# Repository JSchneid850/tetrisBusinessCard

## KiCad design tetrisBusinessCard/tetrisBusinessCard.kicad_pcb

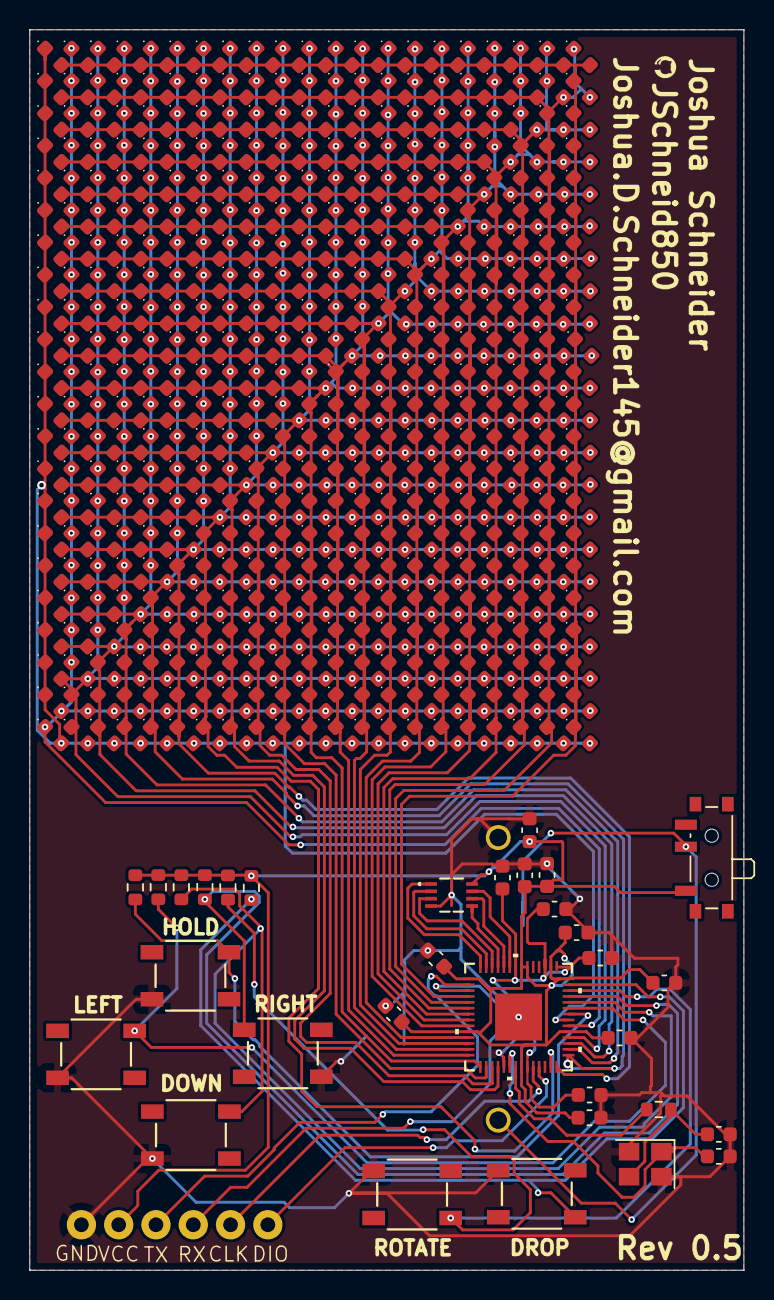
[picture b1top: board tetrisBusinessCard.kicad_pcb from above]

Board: 2 copper layers, 48.7 x 84.5 mm, 497 parts (1 on the bottom side), 45 nets.

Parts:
B1: BS-02-A1BK007; BAT_BS-02_MYG-NoDrill
C1, C2, C3, C4, C5, C7, C9, C10, C11, C12, C13: 100n; C_0603_1608Metric
C6, C8: 1u; C_0603_1608Metric
C16, C17: 15p; C_0603_1608Metric
D1, D2, D3, D4, D5, D6, D7, D8, D9, D10, D11, D12, D13, D14, D15, D16, D17, D18, D19, D20, D21, D22, D23, D24, D25, D26, D27, D28, D29, D30, D31, D32, D33, D34, D35, D36, D37, D38, D39, D40, D41, D42, D43, D44, D45, D46, D47, D48, D49, D50, D51, D52, D53, D54, D55, D56, D57, D58, D59, D60, D61, D62, D63, D64, D65, D66, D67, D68, D69, D70, D71, D72, D73, D74, D75, D76, D77, D78, D79, D80, D81, D82, D83, D84, D85, D86, D87, D88, D89, D90, D91, D92, D93, D94, D95, D96, D97, D98, D99, D100, D101, D102, D103, D104, D105, D106, D107, D108, D109, D110, D111, D112, D113, D114, D115, D116, D117, D118, D119, D120, D121, D122, D123, D124, D125, D126, D127, D128, D129, D130, D131, D132, D133, D134, D135, D136, D137, D138, D139, D140, D141, D142, D143, D144, D145, D146, D147, D148, D149, D150, D151, D152, D153, D154, D155, D156, D157, D158, D159, D160, D161, D162, D163, D164, D165, D166, D167, D168, D169, D170, D171, D172, D173, D174, D175, D176, D177, D178, D179, D180, D181, D182, D183, D184, D185, D186, D187, D188, D189, D190, D191, D192, D193, D194, D195, D196, D197, D198, D199, D200, D201, D202, D203, D204, D205, D206, D207, D208, D209, D210, D211, D212, D213, D214, D215, D216, D217, D218, D219, D220, D221, D222, D223, D224, D225, D226, D227, D228, D229, D230, D231, D232, D233, D234, D235, D236, D237, D238, D239, D240, D241, D242, D243, D244, D245, D246, D247, D248, D249, D250, D251, D252, D253, D254, D255, D256, D257, D258, D259, D260, D261, D262, D263, D264, D265, D266, D267, D268, D269, D270, D271, D272, D273, D274, D275, D276, D277, D278, D279, D280, D281, D282, D283, D284, D285, D286, D287, D288, D289, D290, D291, D292, D293, D294, D295, D296, D297, D298, D299, D300, D301, D302, D303, D304, D305, D306, D307, D308, D309, D310, D311, D312, D313, D314, D315, D316, D317, D318, D319, D320, D321, D322, D323, D324, D325, D326, D327, D328, D329, D330, D331, D332, D333, D334, D335, D336, D337, D338, D339, D340, D341, D342, D343, D344, D345, D346, D347, D348, D349, D350, D351, D352, D353, D354, D355, D356, D357, D358, D359, D360, D361, D362, D363, D364, D365, D366, D367, D368, D369, D370, D371, D372, D373, D374, D375, D376, D377, D378, D379, D380, D381, D382, D383, D384, D385, D386, D387, D388, D389, D390, D391, D392, D393, D394, D395, D396, D397, D398, D399, D400, D401, D402, D403, D404, D405, D406, D407, D408, D409, D410, D411, D412, D413, D414, D415, D416, D417, D418, D419, D420, D421, D422, D423, D424, D425, D426, D427, D428, D429, D430, D431, D432, D433, D434, D435, D436, D437, D438, D439, D440, D441, D442, D443, D444, D445, D446, D447, D448, D449, D450, D451, D452, D453, D454, D455, D456, D457, D458, D459, D460, D461, D462: LED; LED_0603_1608MetricAdjusted
Github: LOGO; 2mgh
PogoConnector1: PogoConnector
R5: 1kΩ; R_0603_1608Metric
R6, R7, R8, R9, R10, R11: 10kΩ; R_0603_1608Metric
SW1, SW2, SW3, SW4, SW5, SW6: SW_Push; SW_PTS647SM38SMTR2LFS_CNK
SW7: SW_DPST_x2; SW_SPDT_PCM12
U1: SC091413; QFN56_7X7_RPI
U2: W25Q16JVUXIQ; W25Q16JVUXIQ_WIN
Y1: ABMB-272-T3; Crystal_SMD_3225-4Pin_3.2x2.5mm

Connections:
+1V1: C1.2, C6.2, C7.2, C12.1, U1.23 (DVDD), U1.43 (ADC_AVDD), U1.45 (VREG_VOUT), U1.50 (DVDD)
BATT +: C2.2, C3.2, C4.2, C5.2, C8.2, C9.2, C10.1, C11.1, C13.1, PogoConnector1.2, R6.1, R7.1, R8.1, R9.1, R10.1, R11.1, SW7.1 (A), U1.1 (IOVDD), U1.10 (IOVDD), U1.22 (IOVDD), U1.33 (IOVDD), U1.42 (IOVDD), U1.44 (VREG_VIN), U1.48 (USB_VDD), U1.49 (IOVDD), U2.8 (VCC)
BTN_1: R10.2, SW1.3, U1.36 (GPIO24)
BTN_2: R9.2, SW2.3, U1.37 (GPIO25)
BTN_3: R8.2, SW3.3, U1.38 (GPIO26/ADC0)
BTN_4: R7.2, SW4.1, U1.39 (GPIO27/ADC1)
BTN_5: R6.2, SW5.1, U1.40 (GPIO28/ADC2)
BTN_6: R11.2, SW6.1, U1.41 (GPIO29/ADC3)
CHRLY_1: D1.2 (A), D2.2 (A), D3.2 (A), D4.2 (A), D5.2 (A), D6.2 (A), D7.2 (A), D8.2 (A), D9.2 (A), D10.2 (A), D11.2 (A), D12.2 (A), D13.2 (A), D14.2 (A), D15.2 (A), D16.2 (A), D17.2 (A), D18.2 (A), D19.2 (A), D20.2 (A), D21.2 (A), D22.1 (K), D43.1 (K), D64.1 (K), D85.1 (K), D106.1 (K), D127.1 (K), D148.1 (K), D169.1 (K), D190.1 (K), D211.1 (K), D232.1 (K), D253.1 (K), D274.1 (K), D295.1 (K), D316.1 (K), D337.1 (K), D358.1 (K), D379.1 (K), D400.1 (K), D421.1 (K), D442.1 (K), U1.4 (GPIO2)
CHRLY_2: D1.1 (K), D22.2 (A), D23.2 (A), D24.2 (A), D25.2 (A), D26.2 (A), D27.2 (A), D28.2 (A), D29.2 (A), D30.2 (A), D31.2 (A), D32.2 (A), D33.2 (A), D34.2 (A), D35.2 (A), D36.2 (A), D37.2 (A), D38.2 (A), D39.2 (A), D40.2 (A), D41.2 (A), D42.2 (A), D44.1 (K), D65.1 (K), D86.1 (K), D107.1 (K), D128.1 (K), D149.1 (K), D170.1 (K), D191.1 (K), D212.1 (K), D233.1 (K), D254.1 (K), D275.1 (K), D296.1 (K), D317.1 (K), D338.1 (K), D359.1 (K), D380.1 (K), D401.1 (K), D422.1 (K), D443.1 (K), U1.5 (GPIO3)
CHRLY_3: D2.1 (K), D23.1 (K), D43.2 (A), D44.2 (A), D45.2 (A), D46.2 (A), D47.2 (A), D48.2 (A), D49.2 (A), D50.2 (A), D51.2 (A), D52.2 (A), D53.2 (A), D54.2 (A), D55.2 (A), D56.2 (A), D57.2 (A), D58.2 (A), D59.2 (A), D60.2 (A), D61.2 (A), D62.2 (A), D63.2 (A), D66.1 (K), D87.1 (K), D108.1 (K), D129.1 (K), D150.1 (K), D171.1 (K), D192.1 (K), D213.1 (K), D234.1 (K), D255.1 (K), D276.1 (K), D297.1 (K), D318.1 (K), D339.1 (K), D360.1 (K), D381.1 (K), D402.1 (K), D423.1 (K), D444.1 (K), U1.6 (GPIO4)
CHRLY_4: D3.1 (K), D24.1 (K), D45.1 (K), D64.2 (A), D65.2 (A), D66.2 (A), D67.2 (A), D68.2 (A), D69.2 (A), D70.2 (A), D71.2 (A), D72.2 (A), D73.2 (A), D74.2 (A), D75.2 (A), D76.2 (A), D77.2 (A), D78.2 (A), D79.2 (A), D80.2 (A), D81.2 (A), D82.2 (A), D83.2 (A), D84.2 (A), D88.1 (K), D109.1 (K), D130.1 (K), D151.1 (K), D172.1 (K), D193.1 (K), D214.1 (K), D235.1 (K), D256.1 (K), D277.1 (K), D298.1 (K), D319.1 (K), D340.1 (K), D361.1 (K), D382.1 (K), D403.1 (K), D424.1 (K), D445.1 (K), U1.7 (GPIO5)
CHRLY_5: D4.1 (K), D25.1 (K), D46.1 (K), D67.1 (K), D85.2 (A), D86.2 (A), D87.2 (A), D88.2 (A), D89.2 (A), D90.2 (A), D91.2 (A), D92.2 (A), D93.2 (A), D94.2 (A), D95.2 (A), D96.2 (A), D97.2 (A), D98.2 (A), D99.2 (A), D100.2 (A), D101.2 (A), D102.2 (A), D103.2 (A), D104.2 (A), D105.2 (A), D110.1 (K), D131.1 (K), D152.1 (K), D173.1 (K), D194.1 (K), D215.1 (K), D236.1 (K), D257.1 (K), D278.1 (K), D299.1 (K), D320.1 (K), D341.1 (K), D362.1 (K), D383.1 (K), D404.1 (K), D425.1 (K), D446.1 (K), U1.8 (GPIO6)
CHRLY_6: D5.1 (K), D26.1 (K), D47.1 (K), D68.1 (K), D89.1 (K), D106.2 (A), D107.2 (A), D108.2 (A), D109.2 (A), D110.2 (A), D111.2 (A), D112.2 (A), D113.2 (A), D114.2 (A), D115.2 (A), D116.2 (A), D117.2 (A), D118.2 (A), D119.2 (A), D120.2 (A), D121.2 (A), D122.2 (A), D123.2 (A), D124.2 (A), D125.2 (A), D126.2 (A), D132.1 (K), D153.1 (K), D174.1 (K), D195.1 (K), D216.1 (K), D237.1 (K), D258.1 (K), D279.1 (K), D300.1 (K), D321.1 (K), D342.1 (K), D363.1 (K), D384.1 (K), D405.1 (K), D426.1 (K), D447.1 (K), U1.9 (GPIO7)
CHRLY_7: D6.1 (K), D27.1 (K), D48.1 (K), D69.1 (K), D90.1 (K), D111.1 (K), D127.2 (A), D128.2 (A), D129.2 (A), D130.2 (A), D131.2 (A), D132.2 (A), D133.2 (A), D134.2 (A), D135.2 (A), D136.2 (A), D137.2 (A), D138.2 (A), D139.2 (A), D140.2 (A), D141.2 (A), D142.2 (A), D143.2 (A), D144.2 (A), D145.2 (A), D146.2 (A), D147.2 (A), D154.1 (K), D175.1 (K), D196.1 (K), D217.1 (K), D238.1 (K), D259.1 (K), D280.1 (K), D301.1 (K), D322.1 (K), D343.1 (K), D364.1 (K), D385.1 (K), D406.1 (K), D427.1 (K), D448.1 (K), U1.11 (GPIO8)
CHRLY_8: D7.1 (K), D28.1 (K), D49.1 (K), D70.1 (K), D91.1 (K), D112.1 (K), D133.1 (K), D148.2 (A), D149.2 (A), D150.2 (A), D151.2 (A), D152.2 (A), D153.2 (A), D154.2 (A), D155.2 (A), D156.2 (A), D157.2 (A), D158.2 (A), D159.2 (A), D160.2 (A), D161.2 (A), D162.2 (A), D163.2 (A), D164.2 (A), D165.2 (A), D166.2 (A), D167.2 (A), D168.2 (A), D176.1 (K), D197.1 (K), D218.1 (K), D239.1 (K), D260.1 (K), D281.1 (K), D302.1 (K), D323.1 (K), D344.1 (K), D365.1 (K), D386.1 (K), D407.1 (K), D428.1 (K), D449.1 (K), U1.12 (GPIO9)
CHRLY_9: D8.1 (K), D29.1 (K), D50.1 (K), D71.1 (K), D92.1 (K), D113.1 (K), D134.1 (K), D155.1 (K), D169.2 (A), D170.2 (A), D171.2 (A), D172.2 (A), D173.2 (A), D174.2 (A), D175.2 (A), D176.2 (A), D177.2 (A), D178.2 (A), D179.2 (A), D180.2 (A), D181.2 (A), D182.2 (A), D183.2 (A), D184.2 (A), D185.2 (A), D186.2 (A), D187.2 (A), D188.2 (A), D189.2 (A), D198.1 (K), D219.1 (K), D240.1 (K), D261.1 (K), D282.1 (K), D303.1 (K), D324.1 (K), D345.1 (K), D366.1 (K), D387.1 (K), D408.1 (K), D429.1 (K), D450.1 (K), U1.13 (GPIO10)
CHRLY_10: D9.1 (K), D30.1 (K), D51.1 (K), D72.1 (K), D93.1 (K), D114.1 (K), D135.1 (K), D156.1 (K), D177.1 (K), D190.2 (A), D191.2 (A), D192.2 (A), D193.2 (A), D194.2 (A), D195.2 (A), D196.2 (A), D197.2 (A), D198.2 (A), D199.2 (A), D200.2 (A), D201.2 (A), D202.2 (A), D203.2 (A), D204.2 (A), D205.2 (A), D206.2 (A), D207.2 (A), D208.2 (A), D209.2 (A), D210.2 (A), D220.1 (K), D241.1 (K), D262.1 (K), D283.1 (K), D304.1 (K), D325.1 (K), D346.1 (K), D367.1 (K), D388.1 (K), D409.1 (K), D430.1 (K), D451.1 (K), U1.14 (GPIO11)
CHRLY_11: D10.1 (K), D31.1 (K), D52.1 (K), D73.1 (K), D94.1 (K), D115.1 (K), D136.1 (K), D157.1 (K), D178.1 (K), D199.1 (K), D211.2 (A), D212.2 (A), D213.2 (A), D214.2 (A), D215.2 (A), D216.2 (A), D217.2 (A), D218.2 (A), D219.2 (A), D220.2 (A), D221.2 (A), D222.2 (A), D223.2 (A), D224.2 (A), D225.2 (A), D226.2 (A), D227.2 (A), D228.2 (A), D229.2 (A), D230.2 (A), D231.2 (A), D242.1 (K), D263.1 (K), D284.1 (K), D305.1 (K), D326.1 (K), D347.1 (K), D368.1 (K), D389.1 (K), D410.1 (K), D431.1 (K), D452.1 (K), U1.15 (GPIO12)
CHRLY_12: D11.1 (K), D32.1 (K), D53.1 (K), D74.1 (K), D95.1 (K), D116.1 (K), D137.1 (K), D158.1 (K), D179.1 (K), D200.1 (K), D221.1 (K), D232.2 (A), D233.2 (A), D234.2 (A), D235.2 (A), D236.2 (A), D237.2 (A), D238.2 (A), D239.2 (A), D240.2 (A), D241.2 (A), D242.2 (A), D243.2 (A), D244.2 (A), D245.2 (A), D246.2 (A), D247.2 (A), D248.2 (A), D249.2 (A), D250.2 (A), D251.2 (A), D252.2 (A), D264.1 (K), D285.1 (K), D306.1 (K), D327.1 (K), D348.1 (K), D369.1 (K), D390.1 (K), D411.1 (K), D432.1 (K), D453.1 (K), U1.16 (GPIO13)
CHRLY_13: D12.1 (K), D33.1 (K), D54.1 (K), D75.1 (K), D96.1 (K), D117.1 (K), D138.1 (K), D159.1 (K), D180.1 (K), D201.1 (K), D222.1 (K), D243.1 (K), D253.2 (A), D254.2 (A), D255.2 (A), D256.2 (A), D257.2 (A), D258.2 (A), D259.2 (A), D260.2 (A), D261.2 (A), D262.2 (A), D263.2 (A), D264.2 (A), D265.2 (A), D266.2 (A), D267.2 (A), D268.2 (A), D269.2 (A), D270.2 (A), D271.2 (A), D272.2 (A), D273.2 (A), D286.1 (K), D307.1 (K), D328.1 (K), D349.1 (K), D370.1 (K), D391.1 (K), D412.1 (K), D433.1 (K), D454.1 (K), U1.17 (GPIO14)
CHRLY_14: D13.1 (K), D34.1 (K), D55.1 (K), D76.1 (K), D97.1 (K), D118.1 (K), D139.1 (K), D160.1 (K), D181.1 (K), D202.1 (K), D223.1 (K), D244.1 (K), D265.1 (K), D274.2 (A), D275.2 (A), D276.2 (A), D277.2 (A), D278.2 (A), D279.2 (A), D280.2 (A), D281.2 (A), D282.2 (A), D283.2 (A), D284.2 (A), D285.2 (A), D286.2 (A), D287.2 (A), D288.2 (A), D289.2 (A), D290.2 (A), D291.2 (A), D292.2 (A), D293.2 (A), D294.2 (A), D308.1 (K), D329.1 (K), D350.1 (K), D371.1 (K), D392.1 (K), D413.1 (K), D434.1 (K), D455.1 (K), U1.18 (GPIO15)
CHRLY_15: D14.1 (K), D35.1 (K), D56.1 (K), D77.1 (K), D98.1 (K), D119.1 (K), D140.1 (K), D161.1 (K), D182.1 (K), D203.1 (K), D224.1 (K), D245.1 (K), D266.1 (K), D287.1 (K), D295.2 (A), D296.2 (A), D297.2 (A), D298.2 (A), D299.2 (A), D300.2 (A), D301.2 (A), D302.2 (A), D303.2 (A), D304.2 (A), D305.2 (A), D306.2 (A), D307.2 (A), D308.2 (A), D309.2 (A), D310.2 (A), D311.2 (A), D312.2 (A), D313.2 (A), D314.2 (A), D315.2 (A), D330.1 (K), D351.1 (K), D372.1 (K), D393.1 (K), D414.1 (K), D435.1 (K), D456.1 (K), U1.27 (GPIO16)
CHRLY_16: D15.1 (K), D36.1 (K), D57.1 (K), D78.1 (K), D99.1 (K), D120.1 (K), D141.1 (K), D162.1 (K), D183.1 (K), D204.1 (K), D225.1 (K), D246.1 (K), D267.1 (K), D288.1 (K), D309.1 (K), D316.2 (A), D317.2 (A), D318.2 (A), D319.2 (A), D320.2 (A), D321.2 (A), D322.2 (A), D323.2 (A), D324.2 (A), D325.2 (A), D326.2 (A), D327.2 (A), D328.2 (A), D329.2 (A), D330.2 (A), D331.2 (A), D332.2 (A), D333.2 (A), D334.2 (A), D335.2 (A), D336.2 (A), D352.1 (K), D373.1 (K), D394.1 (K), D415.1 (K), D436.1 (K), D457.1 (K), U1.28 (GPIO17)
CHRLY_17: D16.1 (K), D37.1 (K), D58.1 (K), D79.1 (K), D100.1 (K), D121.1 (K), D142.1 (K), D163.1 (K), D184.1 (K), D205.1 (K), D226.1 (K), D247.1 (K), D268.1 (K), D289.1 (K), D310.1 (K), D331.1 (K), D337.2 (A), D338.2 (A), D339.2 (A), D340.2 (A), D341.2 (A), D342.2 (A), D343.2 (A), D344.2 (A), D345.2 (A), D346.2 (A), D347.2 (A), D348.2 (A), D349.2 (A), D350.2 (A), D351.2 (A), D352.2 (A), D353.2 (A), D354.2 (A), D355.2 (A), D356.2 (A), D357.2 (A), D374.1 (K), D395.1 (K), D416.1 (K), D437.1 (K), D458.1 (K), U1.29 (GPIO18)
CHRLY_18: D17.1 (K), D38.1 (K), D59.1 (K), D80.1 (K), D101.1 (K), D122.1 (K), D143.1 (K), D164.1 (K), D185.1 (K), D206.1 (K), D227.1 (K), D248.1 (K), D269.1 (K), D290.1 (K), D311.1 (K), D332.1 (K), D353.1 (K), D358.2 (A), D359.2 (A), D360.2 (A), D361.2 (A), D362.2 (A), D363.2 (A), D364.2 (A), D365.2 (A), D366.2 (A), D367.2 (A), D368.2 (A), D369.2 (A), D370.2 (A), D371.2 (A), D372.2 (A), D373.2 (A), D374.2 (A), D375.2 (A), D376.2 (A), D377.2 (A), D378.2 (A), D396.1 (K), D417.1 (K), D438.1 (K), D459.1 (K), U1.30 (GPIO19)
CHRLY_19: D18.1 (K), D39.1 (K), D60.1 (K), D81.1 (K), D102.1 (K), D123.1 (K), D144.1 (K), D165.1 (K), D186.1 (K), D207.1 (K), D228.1 (K), D249.1 (K), D270.1 (K), D291.1 (K), D312.1 (K), D333.1 (K), D354.1 (K), D375.1 (K), D379.2 (A), D380.2 (A), D381.2 (A), D382.2 (A), D383.2 (A), D384.2 (A), D385.2 (A), D386.2 (A), D387.2 (A), D388.2 (A), D389.2 (A), D390.2 (A), D391.2 (A), D392.2 (A), D393.2 (A), D394.2 (A), D395.2 (A), D396.2 (A), D397.2 (A), D398.2 (A), D399.2 (A), D418.1 (K), D439.1 (K), D460.1 (K), U1.31 (GPIO20)
CHRLY_20: D19.1 (K), D40.1 (K), D61.1 (K), D82.1 (K), D103.1 (K), D124.1 (K), D145.1 (K), D166.1 (K), D187.1 (K), D208.1 (K), D229.1 (K), D250.1 (K), D271.1 (K), D292.1 (K), D313.1 (K), D334.1 (K), D355.1 (K), D376.1 (K), D397.1 (K), D400.2 (A), D401.2 (A), D402.2 (A), D403.2 (A), D404.2 (A), D405.2 (A), D406.2 (A), D407.2 (A), D408.2 (A), D409.2 (A), D410.2 (A), D411.2 (A), D412.2 (A), D413.2 (A), D414.2 (A), D415.2 (A), D416.2 (A), D417.2 (A), D418.2 (A), D419.2 (A), D420.2 (A), D440.1 (K), D461.1 (K), U1.32 (GPIO21)
CHRLY_21: D20.1 (K), D41.1 (K), D62.1 (K), D83.1 (K), D104.1 (K), D125.1 (K), D146.1 (K), D167.1 (K), D188.1 (K), D209.1 (K), D230.1 (K), D251.1 (K), D272.1 (K), D293.1 (K), D314.1 (K), D335.1 (K), D356.1 (K), D377.1 (K), D398.1 (K), D419.1 (K), D421.2 (A), D422.2 (A), D423.2 (A), D424.2 (A), D425.2 (A), D426.2 (A), D427.2 (A), D428.2 (A), D429.2 (A), D430.2 (A), D431.2 (A), D432.2 (A), D433.2 (A), D434.2 (A), D435.2 (A), D436.2 (A), D437.2 (A), D438.2 (A), D439.2 (A), D440.2 (A), D441.2 (A), D462.1 (K), U1.34 (GPIO22)
CHRLY_22: D21.1 (K), D42.1 (K), D63.1 (K), D84.1 (K), D105.1 (K), D126.1 (K), D147.1 (K), D168.1 (K), D189.1 (K), D210.1 (K), D231.1 (K), D252.1 (K), D273.1 (K), D294.1 (K), D315.1 (K), D336.1 (K), D357.1 (K), D378.1 (K), D399.1 (K), D420.1 (K), D441.1 (K), D442.2 (A), D443.2 (A), D444.2 (A), D445.2 (A), D446.2 (A), D447.2 (A), D448.2 (A), D449.2 (A), D450.2 (A), D451.2 (A), D452.2 (A), D453.2 (A), D454.2 (A), D455.2 (A), D456.2 (A), D457.2 (A), D458.2 (A), D459.2 (A), D460.2 (A), D461.2 (A), D462.2 (A), U1.35 (GPIO23)
GND: B1.2, C1.1, C2.1, C3.1, C4.1, C5.1, C6.1, C7.1, C8.1, C9.1, C10.2, C11.2, C12.2, C13.2, C16.2, C17.2, PogoConnector1.1, SW1.2, SW2.2, SW3.2, SW4.4, SW5.4, SW6.4, U1.19 (TESTEN), U1.57 (GND), U2.4 (GND), U2.9 (EPAD), Y1.2, Y1.4
unnamed: C17.1, R5.2, Y1.3
unnamed: B1.1, SW7.2 (B)
unnamed: U1.52 (SQPI_SCLK), U2.6 (CLK)
unnamed: U1.53 (SQPI_SD0), U2.5 (DI(IO0))
unnamed: U1.55 (SQPI_SD1), U2.2 (DO(IO1))
unnamed: U1.54 (SQPI_SD2), U2.3 (/WP(IO2))
unnamed: U1.51 (SQPI_SD3), U2.7 (/HOLD_or_/RESET(IO3))
unnamed: U1.56 (SQPI_SS_N), U2.1 (/CS)
RX: PogoConnector1.4, U1.3 (GPIO1)
SWCLK: PogoConnector1.5, U1.24 (SWCLK)
SWDIO: PogoConnector1.6, U1.25 (SWDIO)
TX: PogoConnector1.3, U1.2 (GPIO0)
XIn: C16.1, U1.20 (XIN), Y1.1
Xout: R5.1, U1.21 (XOUT)

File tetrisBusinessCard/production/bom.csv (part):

Designator,Footprint,Quantity,Value,LCSC Part #
"B1_8, B1_7, B1_6, B1_5, B1_4, B1_3, B1_2, B1",BAT_BS-02_MYG-NoDrill,8,BS-02-A1BK007,
"C1_8, C1_7, C1_6, C1_5, C1_4, C1_3, C1_2, C1, C10_8, C10_7, C10_6, C10_5, C10_4, C10_3, C10_2, C10, C11_8, C11_7, C11_6, C11_5, C11_4, C11_3, C11_2, C11, C12_8, C12_7, C12_6, C12_5, C12_4, C12_3, C12_2, C12, C13_8, C13_7, C13_6, C13_5, C13_4, C13_3, C13_2, C13, C2_8, C2_7, C2_6, C2_5, C2_4, C2_3, C2_2, C2, C3_8, C3_7, C3_6, C3_5, C3_4, C3_3, C3_2, C3, C4_8, C4_7, C4_6, C4_5, C4_4, C4_3, C4_2, C4, C5_8, C5_7, C5_6, C5_5, C5_4, C5_3, C5_2, C5, C7_8, C7_7, C7_6, C7_5, C7_4, C7_3, C7_2, C7, C9_8, C9_7, C9_6, C9_5, C9_4, C9_3, C9_2, C9",0603,88,100n,
"C16_8, C16_7, C16_6, C16_5, C16_4, C16_3, C16_2, C16, C17_8, C17_7, C17_6, C17_5, C17_4, C17_3, C17_2, C17",0603,16,15p,
"C6_8, C6_7, C6_6, C6_5, C6_4, C6_3, C6_2, C6, C8_8, C8_7, C8_6, C8_5, C8_4, C8_3, C8_2, C8",0603,16,1u,
"D1_8, D1_7, D1_6, D1_5, D1_4, D1_3, D1_2, D1, D10_8, D10_7, D10_6, D10_5, D10_4, D10_3, D10_2, D10, D100_8, D100_7, D100_6, D100_5, D100_4, D100_3, D100_2, D100, D101_8, D101_7, D101_6, D101_5, D101_4, D101_3, D101_2, D101, D102_8, D102_7, D102_6, D102_5, D102_4, D102_3, D102_2, D102, D103_8, D103_7, D103_6, D103_5, D103_4, D103_3, D103_2, D103, D104_8, D104_7, D104_6, D104_5, D104_4, D104_3, D104_2, D104, D105_8, D105_7, D105_6, D105_5, D105_4, D105_3, D105_2, D105, D106_8, D106_7, D106_6, D106_5, D106_4, D106_3, D106_2, D106, D107_8, D107_7, D107_6, D107_5, D107_4, D107_3, D107_2, D107, D108_8, D108_7, D108_6, D108_5, D108_4, D108_3, D108_2, D108, D109_8, D109_7, D109_6, D109_5, D109_4, D109_3, D109_2, D109, D11_8, D11_7, D11_6, D11_5, D11_4, D11_3, D11_2, D11, D110_8, D110_7, D110_6, D110_5, D110_4, D110_3, D110_2, D110, D111_8, D111_7, D111_6, D111_5, D111_4, D111_3, D111_2, D111, D112_8, D112_7, D112_6, D112_5, D112_4, D112_3, D112_2, D112, D113_8, D113_7, D113_6, D113_5, D113_4, D113_3, D113_2, D113, D114_8, D114_7, D114_6, D114_5, D114_4, D114_3, D114_2, D114, D115_8, D115_7, D115_6, D115_5, D115_4, D115_3, D115_2, D115, D116_8, D116_7, D116_6, D116_5, D116_4, D116_3, D116_2, D116, D117_8, D117_7, D117_6, D117_5, D117_4, D117_3, D117_2, D117, D118_8, D118_7, D118_6, D118_5, D118_4, D118_3, D118_2, D118, D119_8, D119_7, D119_6, D119_5, D119_4, D119_3, D119_2, D119, D12_8, D12_7, D12_6, D12_5, D12_4, D12_3, D12_2, D12, D120_8, D120_7, D120_6, D120_5, D120_4, D120_3, D120_2, D120",0603,200,LED,
"D121_8, D121_7, D121_6, D121_5, D121_4, D121_3, D121_2, D121, D122_8, D122_7, D122_6, D122_5, D122_4, D122_3, D122_2, D122, D123_8, D123_7, D123_6, D123_5, D123_4, D123_3, D123_2, D123, D124_8, D124_7, D124_6, D124_5, D124_4, D124_3, D124_2, D124, D125_8, D125_7, D125_6, D125_5, D125_4, D125_3, D125_2, D125, D126_8, D126_7, D126_6, D126_5, D126_4, D126_3, D126_2, D126, D127_8, D127_7, D127_6, D127_5, D127_4, D127_3, D127_2, D127, D128_8, D128_7, D128_6, D128_5, D128_4, D128_3, D128_2, D128, D129_8, D129_7, D129_6, D129_5, D129_4, D129_3, D129_2, D129, D13_8, D13_7, D13_6, D13_5, D13_4, D13_3, D13_2, D13, D130_8, D130_7, D130_6, D130_5, D130_4, D130_3, D130_2, D130, D131_8, D131_7, D131_6, D131_5, D131_4, D131_3, D131_2, D131, D132_8, D132_7, D132_6, D132_5, D132_4, D132_3, D132_2, D132, D133_8, D133_7, D133_6, D133_5, D133_4, D133_3, D133_2, D133, D134_8, D134_7, D134_6, D134_5, D134_4, D134_3, D134_2, D134, D135_8, D135_7, D135_6, D135_5, D135_4, D135_3, D135_2, D135, D136_8, D136_7, D136_6, D136_5, D136_4, D136_3, D136_2, D136, D137_8, D137_7, D137_6, D137_5, D137_4, D137_3, D137_2, D137, D138_8, D138_7, D138_6, D138_5, D138_4, D138_3, D138_2, D138, D139_8, D139_7, D139_6, D139_5, D139_4, D139_3, D139_2, D139, D14_8, D14_7, D14_6, D14_5, D14_4, D14_3, D14_2, D14, D140_8, D140_7, D140_6, D140_5, D140_4, D140_3, D140_2, D140, D141_8, D141_7, D141_6, D141_5, D141_4, D141_3, D141_2, D141, D142_8, D142_7, D142_6, D142_5, D142_4, D142_3, D142_2, D142, D143_8, D143_7, D143_6, D143_5, D143_4, D143_3, D143_2, D143",0603,200,LED,
"D144_8, D144_7, D144_6, D144_5, D144_4, D144_3, D144_2, D144, D145_8, D145_7, D145_6, D145_5, D145_4, D145_3, D145_2, D145, D146_8, D146_7, D146_6, D146_5, D146_4, D146_3, D146_2, D146, D147_8, D147_7, D147_6, D147_5, D147_4, D147_3, D147_2, D147, D148_8, D148_7, D148_6, D148_5, D148_4, D148_3, D148_2, D148, D149_8, D149_7, D149_6, D149_5, D149_4, D149_3, D149_2, D149, D15_8, D15_7, D15_6, D15_5, D15_4, D15_3, D15_2, D15, D150_8, D150_7, D150_6, D150_5, D150_4, D150_3, D150_2, D150, D151_8, D151_7, D151_6, D151_5, D151_4, D151_3, D151_2, D151, D152_8, D152_7, D152_6, D152_5, D152_4, D152_3, D152_2, D152, D153_8, D153_7, D153_6, D153_5, D153_4, D153_3, D153_2, D153, D154_8, D154_7, D154_6, D154_5, D154_4, D154_3, D154_2, D154, D155_8, D155_7, D155_6, D155_5, D155_4, D155_3, D155_2, D155, D156_8, D156_7, D156_6, D156_5, D156_4, D156_3, D156_2, D156, D157_8, D157_7, D157_6, D157_5, D157_4, D157_3, D157_2, D157, D158_8, D158_7, D158_6, D158_5, D158_4, D158_3, D158_2, D158, D159_8, D159_7, D159_6, D159_5, D159_4, D159_3, D159_2, D159, D16_8, D16_7, D16_6, D16_5, D16_4, D16_3, D16_2, D16, D160_8, D160_7, D160_6, D160_5, D160_4, D160_3, D160_2, D160, D161_8, D161_7, D161_6, D161_5, D161_4, D161_3, D161_2, D161, D162_8, D162_7, D162_6, D162_5, D162_4, D162_3, D162_2, D162, D163_8, D163_7, D163_6, D163_5, D163_4, D163_3, D163_2, D163, D164_8, D164_7, D164_6, D164_5, D164_4, D164_3, D164_2, D164, D165_8, D165_7, D165_6, D165_5, D165_4, D165_3, D165_2, D165, D166_8, D166_7, D166_6, D166_5, D166_4, D166_3, D166_2, D166",0603,200,LED,
"D167_8, D167_7, D167_6, D167_5, D167_4, D167_3, D167_2, D167, D168_8, D168_7, D168_6, D168_5, D168_4, D168_3, D168_2, D168, D169_8, D169_7, D169_6, D169_5, D169_4, D169_3, D169_2, D169, D17_8, D17_7, D17_6, D17_5, D17_4, D17_3, D17_2, D17, D170_8, D170_7, D170_6, D170_5, D170_4, D170_3, D170_2, D170, D171_8, D171_7, D171_6, D171_5, D171_4, D171_3, D171_2, D171, D172_8, D172_7, D172_6, D172_5, D172_4, D172_3, D172_2, D172, D173_8, D173_7, D173_6, D173_5, D173_4, D173_3, D173_2, D173, D174_8, D174_7, D174_6, D174_5, D174_4, D174_3, D174_2, D174, D175_8, D175_7, D175_6, D175_5, D175_4, D175_3, D175_2, D175, D176_8, D176_7, D176_6, D176_5, D176_4, D176_3, D176_2, D176, D177_8, D177_7, D177_6, D177_5, D177_4, D177_3, D177_2, D177, D178_8, D178_7, D178_6, D178_5, D178_4, D178_3, D178_2, D178, D179_8, D179_7, D179_6, D179_5, D179_4, D179_3, D179_2, D179, D18_8, D18_7, D18_6, D18_5, D18_4, D18_3, D18_2, D18, D180_8, D180_7, D180_6, D180_5, D180_4, D180_3, D180_2, D180, D181_8, D181_7, D181_6, D181_5, D181_4, D181_3, D181_2, D181, D182_8, D182_7, D182_6, D182_5, D182_4, D182_3, D182_2, D182, D183_8, D183_7, D183_6, D183_5, D183_4, D183_3, D183_2, D183, D184_8, D184_7, D184_6, D184_5, D184_4, D184_3, D184_2, D184, D185_8, D185_7, D185_6, D185_5, D185_4, D185_3, D185_2, D185, D186_8, D186_7, D186_6, D186_5, D186_4, D186_3, D186_2, D186, D187_8, D187_7, D187_6, D187_5, D187_4, D187_3, D187_2, D187, D188_8, D188_7, D188_6, D188_5, D188_4, D188_3, D188_2, D188, D189_8, D189_7, D189_6, D189_5, D189_4, D189_3, D189_2, D189",0603,200,LED,
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
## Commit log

2024-10-27 init commit
2024-11-11 update C
2024-11-30 vertical scanning example
2024-12-08 Clean up repo a bit and switch to cpp
2024-12-10 Scaffold charlieplex driver
2024-12-10 start translating driver
2024-12-18 Add capacitive touch symbol and update PCB partially
2024-12-24 pcb rev0.2
2025-01-03 Sync changes from laptop
2025-01-11 Pre 2d array refactor
2025-01-11 Partially done refactor
2025-01-14 done refactoring driver to use 2d arrays
2025-01-18 Fixed vertical scanning! turns out Its not a hardware issue
2025-01-21 Fix driver, now to write tetris
2025-01-22 Create shape, update charlieplex, and begin playfield
2025-01-25 Changes to shape and playfield
2025-01-27 Moving from laptop to desktop
2025-01-29 Fix Write frame issue and clean up usages of cstyle arrays in favor of std::array
2025-01-30 Here's buttons
2025-01-31 Still a few collision errors to figure out
2025-02-05 So close to done, about 4 more features
2025-02-05 Now all I've got left is the score board!
2025-02-05 I'm so close!
2025-02-05 MVP done, now 1 more hardware revision to add back the battery
2025-03-15 RP2040 draws too much power. last commit before switching to stm32 based chips
2025-06-09 Fully Working Card. In need of a re-factor though I dont know what compelled me to not use .h files
2025-06-09 I'll be adding this back soon
2025-08-08 Clean up files and push up final (Bugs not withstanding) version
2026-06-28 commit git ignores?
2026-06-28 update repo to be up to date with laptop backip
2026-06-29 Know working / compileable version w/ all features as of rev0.5
2026-06-30 some more externalControl changes
